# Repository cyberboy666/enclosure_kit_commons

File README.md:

# enclosure_kit_commons
repo to hold the cad files for common parts used in enclosures for underscores products

currently containing cad files for:

## [cap_pot_6mm_shaft](/cap_pot_6mm_shaft)

## [cap_switch_1P2T_tayda_A-659](/cap_switch_1P2T_tayda_A-659)

## [eurorack_power-adapters](/eurorack_power-adapters)

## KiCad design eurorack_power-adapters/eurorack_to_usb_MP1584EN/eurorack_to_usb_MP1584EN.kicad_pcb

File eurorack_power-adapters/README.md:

# eurorack_power-adapters

these are small pcb adapters made to power [underscores.shop](https://underscores.shop) circuits (which primarily run on 5v via usb-a) with a eurorack power supply:

there are a few different options depending on your needs:

## eurorack_to_usb_passive

this is the default adapter that comes with our eurorack enclosure kits - it takes 5v from 16pin eurorack header and passes it to the usb-a jack. 

upside is no external components are needed, only note that your eurorack power supply must already output 5v on this header which some do not

### BOM

part | source
--- | ---
eurorack_to_usb_passive pcb | fab'd from gerber `eurorack_to_usb_passive_mk_i.zip`
USB Type A Connector | [tayda](https://www.taydaelectronics.com/usb-type-a-female-connector.html)
16pin box header | [tayda](https://www.taydaelectronics.com/16-pin-box-header-connector-2-54mm.html)

## eurorack_to_usb_7805

this adapter uses 7805 linear regulator to take 12v from the 10pin eurorack header and convert to 5v (1.5A) over usb-a

upside is will work with any eurorack supply and uses cheap and common parts. downside is linear regulators are not so efficent and loose some energy to heat

### BOM

part | source
--- | ---
eurorack_to_usb_7805 pcb | fab'd from gerber `eurorack_to_usb_7805_mk_i.zip`
USB Type A Connector | [tayda](https://www.taydaelectronics.com/usb-type-a-female-connector.html)
10pin box header | [tayda](https://www.taydaelectronics.com/10-pin-box-header-connector-2-54mm.html)
L7805 to-220 | [tayda](https://www.taydaelectronics.com/lm7805-l7805-7805-voltage-regulator-ic-5v-1-5a.html)
c1 - 0.33u | [tayda](https://www.taydaelectronics.com/10-x-0-33uf-50v-ceramic-disc-capacitor-pkg-of-10.html)
c2 - 0.1u | [tayda](https://www.taydaelectronics.com/a-553-0-1uf-50v-ceramic-disc-capacitor-pkg-of-10.html)

## eurorack_to_usb_MP1584EN

this adapter uses an active switching step-down module to take 12v from 10pin eurorack header down to 5v (3A) over usb-a

upside is it is efficient step down without creating too much heat. downside is requires specific module sourced and costs slightly more

part | source
--- | ---
eurorack_to_usb_MP1584EN pcb | fab'd from gerber `eurorack_to_usb_MP1584EN_mk_i.zip`
USB Type A Connector | [tayda](https://www.taydaelectronics.com/usb-type-a-female-connector.html)
10pin box header | [tayda](https://www.taydaelectronics.com/10-pin-box-header-connector-2-54mm.html)
MP1584EN 3A Step-down 5v | [aliexpress](https://www.aliexpress.com/p/trade/confirm.html?pdp_ext_f=%7B"sku_id":"12000035437063793"%7D)
c1 220u | [tayda](https://www.taydaelectronics.com/220uf-16v-105c-radial-electrolytic-capacitor-6x11mm.html)

# adapting underscores circuits for eurorack

many underscores circuits take 5v from a [horizontal mounted dc barrel jack](https://www.taydaelectronics.com/dc-power-jack-2-1mm-barrel-type-pcb-mount.html) which is good for standalone circuits powered from side. however for eurorack mounted circuits it can be easier to plug in power from behind. in this case we can use a [vertical dc socket](https://www.taydaelectronics.com/dc-power-jack-2-1mm-round-type-panel-mount-1.html) instead. for these sockets the longer pin is GND which goes closest to the edge of pcb.

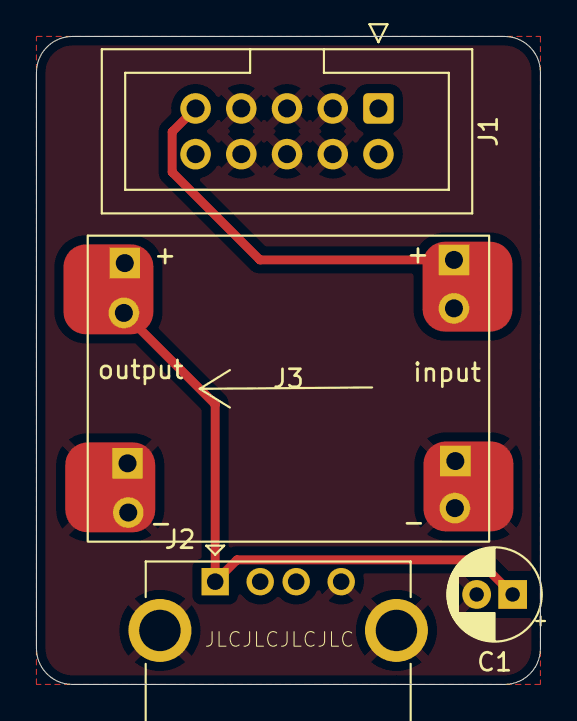
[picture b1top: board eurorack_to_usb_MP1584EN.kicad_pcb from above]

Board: 2 copper layers, 28.0 x 36.0 mm, 4 parts (0 on the bottom side), 3 nets.

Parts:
C1: 220u; CP_Radial_D5.0mm_P2.00mm
J1: power_16pin_eurorack; IDC-Header_2x05_P2.54mm_Vertical
J2: usb-a-horizontal; USB_A_CONNFLY_DS1095-WNR0
J3: MP1584EN_5v_stepdown; MP1584EN_stepdown_module

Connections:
GND: C1.2, J1.3, J1.4, J1.5, J1.6, J1.7, J1.8, J2.4 (GND), J2.5 (Shield), J3.2, J3.3
unnamed: J1.9, J3.1
unnamed: C1.1, J2.1 (VBUS), J3.4

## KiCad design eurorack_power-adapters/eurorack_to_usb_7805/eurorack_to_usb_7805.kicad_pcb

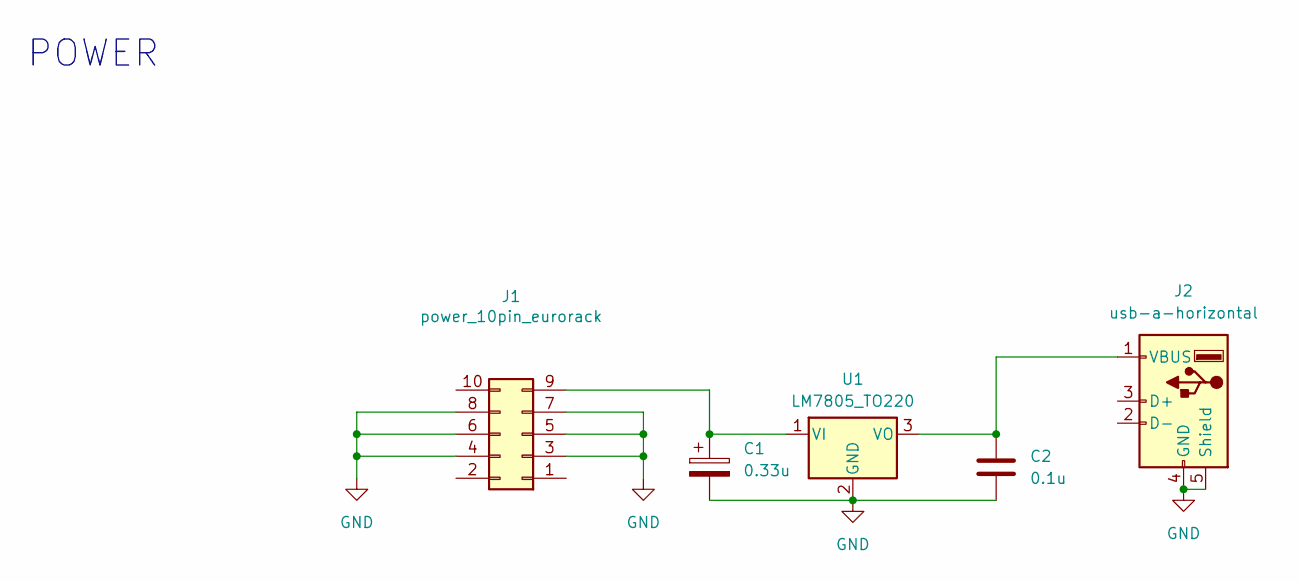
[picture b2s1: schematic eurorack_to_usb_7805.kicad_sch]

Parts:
C1: 0.33u; C_Disc_D5.0mm_W2.5mm_P5.00mm
C2: 0.1u; C_Disc_D5.0mm_W2.5mm_P5.00mm
J1: power_10pin_eurorack; IDC-Header_2x05_P2.54mm_Vertical
J2: usb-a-horizontal; USB_A_CONNFLY_DS1095-WNR0
U1: LM7805_TO220; TO-220F-3_Horizontal_TabDown

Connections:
GND: C1.2, C2.2, J1.3, J1.4, J1.5, J1.6, J1.7, J1.8, J2.4 (GND), J2.5 (Shield), U1.2 (GND)
unnamed: C1.1, J1.9, U1.1 (VI)
unnamed: C2.1, J2.1 (VBUS), U1.3 (VO)

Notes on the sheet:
POWER

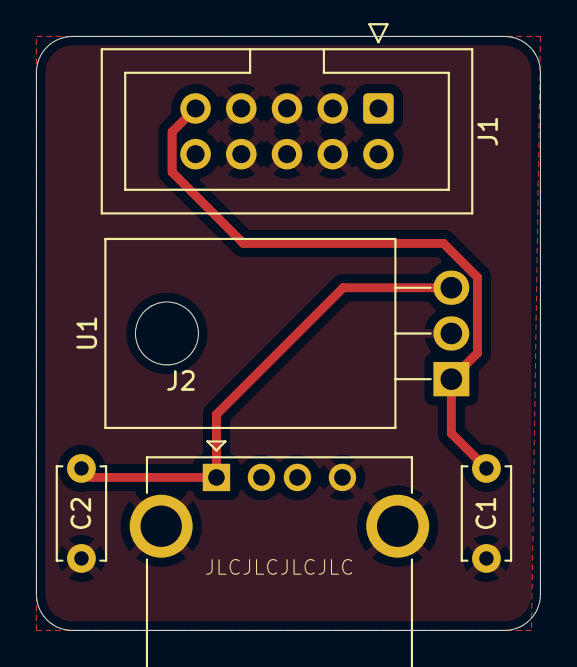
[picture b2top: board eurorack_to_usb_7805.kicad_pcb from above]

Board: 2 copper layers, 28.0 x 33.0 mm, 5 parts (0 on the bottom side), 3 nets.

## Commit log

2025-04-28 add 3d files and pcb files
2025-04-28 remove gerber unzipped
